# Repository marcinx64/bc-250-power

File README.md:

<div align="center">

# BC-250 power controller

**Turn an AMD BC-250 PC and its ATX supply on and off like a console: front button, web UI, and wake by switching on your game controller.**

</div>

The AMD BC-250 is a mining board built around a cut-down PS5 APU, popular as
a cheap gaming PC. It runs from an ATX supply and has only front-panel pads
for its power and reset buttons. This project is a small controller board (a
Seeed XIAO ESP32-C3 and two dual optocouplers) between the supply and the
BC-250 that makes it behave like a console: one button, a web UI, and
power-on by switching on a game controller.

**Status:** the firmware runs on hand-built perfboard controllers. PCB rev A
is designed (ERC and DRC clean) but not yet fabricated or tested.

## Features

**Power control**
- Front button with LED and buzzer: tap to start or shut down, hold to reset,
  hold longer to cut the power. Hold times, beeps and LED are settings.
- Switches the ATX supply (PS_ON#) and presses the BC-250's power and reset
  buttons; reads its power LED to know the real state.
- Runs from +5VSB, so it is reachable whenever the supply is plugged in.

**Wake on controller**
- Switch on a game controller and the PC starts, with no extra hardware.
- Two methods, chosen on the wake page: **BLE** (any Bluetooth LE controller)
  or **2.4G/BT** (2.4G USB-dongle devices and Bluetooth Classic controllers
  such as the DualShock 4).
- Detection uses the ESP32-C3's own radio through its raw capture engine
  (see Credits). Wake lists hold up to 8 BLE devices, or 8 2.4G dongle
  devices and 2 Bluetooth Classic hosts. The re-arm time stops a controller
  that is left on from restarting the PC after shutdown.

**Web UI**
- Dashboard, power control, event log, settings, network, security, themes.
- Setup wizard on first start (`BC250-Setup` network), password, mDNS name
  `bc250.local`, fixed IP or DHCP, WiFi roaming between access points.
- Debug view with a simulated BC-250, so the whole sequence can be tried on
  the bench.

**Safety and updates**
- Update over WiFi from the browser; the previous firmware stays in the
  other slot. Restart and updates keep the PC running (PS_ON is latched
  through a deliberate restart).
- NTP clock, timezone and quiet hours for the buzzer.
- Automatic OS updates of the BC-250 at night over SSH: a silent start, the
  update, a shutdown. A failed or interrupted update ends with the BC-250
  shut down. The update script handles pacman, rpm-ostree with Flatpak,
  and dnf.
- Password-protected UI and API, recovery gesture for a forgotten password.

**Languages**
- Translatable interface with gettext-style catalogs (`docs/TRANSLATING.md`).
  English and Polish ship first; more are welcome.

## How it works

```mermaid
flowchart LR
  PSU["ATX supply<br/>+5VSB, PS_ON#"] -- "+5VSB (power)" --> C
  C["Controller<br/>XIAO ESP32-C3"] -- "PS_ON# via opto" --> PSU
  C -- "power / reset via opto" --> B["BC-250"]
  B -- "power LED (sense)" --> C
  P["Game controller<br/>BLE / 2.4G / BT Classic"] -. "radio" .-> C
  U["Front button, LED, buzzer"] <--> C
  W["Browser"] -- "WiFi, HTTP" --> C
```

The controller is powered from the supply's standby rail and stays on while
the PC is off. When you press the button, use the UI, or switch on a listed
controller, it turns the supply on, waits for the BC-250's power LED, and
pulses the power button if needed. Shutdown is a power-button pulse; the
controller releases the supply when the LED goes dark. Exact behaviour:
[docs/FINAL_FIRMWARE_SPEC.md](docs/FINAL_FIRMWARE_SPEC.md).

## Supported controllers

<!-- devices:start -->

| Device | Mode | Wake method | Status | Tested on | How to add |
|---|---|---|---|---|---|
| 8BitDo Ultimate 2 Wireless Controller | Bluetooth | Bluetooth LE | Works | 2.1.20 | Wake method Bluetooth: Scan while switching it on, add it. |
| 8BitDo Ultimate 2 Wireless Controller | 2.4G dongle | 2.4G dongle (ESB, 1 Mbit/s) | Works | 2.1.20 | Wake method 2.4G: Learn while switching it on with the dongle unplugged. |
| 8BitDo Ultimate 2C Wireless Controller | 2.4G dongle | 2.4G dongle (ESB, 1 Mbit/s) | Works | 2.1.20 | Wake method 2.4G: Learn while switching it on with the dongle unplugged. |
| Nintendo Switch Pro Controller | Bluetooth (classic) | Bluetooth Classic paging | Expected, untested | - | Wake method 2.4G, Bluetooth hosts: type the BC-250's Bluetooth address (bluetoothctl show on the BC-250), or Learn while switching the controller on. |
| Rii mini i25 keyboard | 2.4G dongle | 2.4G dongle (ESB, 1 Mbit/s) | Works | 2.1.20 | Wake method 2.4G: Learn while switching it on with the dongle unplugged. |
| Sony DualSense | Bluetooth (classic) | Bluetooth Classic paging | Expected, untested | - | Wake method 2.4G, Bluetooth hosts: type the BC-250's Bluetooth address (bluetoothctl show on the BC-250), or Learn while switching the controller on. |
| Sony DualShock 4 | Bluetooth (classic) | Bluetooth Classic paging | Works on a spare board, console test pending | 2.2.16 | Wake method 2.4G, Bluetooth hosts: type the BC-250's Bluetooth address (bluetoothctl show on the BC-250), or Learn while switching the controller on. |
| Valve Steam Controller (2.4G dongle) | 2.4G dongle | Other | Help wanted | - | Record it with the dongle unplugged as in docs/SNIFFING.md and open a new-device issue. |

<!-- devices:end -->

Anything speaking Nordic Enhanced ShockBurst (1 Mbit/s, 5-byte address) should
work in 2.4G mode. Add your device: [devices/README.md](devices/README.md).

## Hardware

The tested build is a 40 x 60 mm perfboard; PCB rev A is in
[hardware/](hardware/README.md). Drawings: [schematic](hardware/schematic.svg),
[wiring](hardware/wiring.svg), [bill of materials](hardware/bom.csv).
Full reference: [docs/HARDWARE.md](docs/HARDWARE.md).

| Part | Qty |
|---|---|
| Seeed XIAO ESP32-C3 | 1 |
| TLP521-2 dual optocoupler (rank GB) | 2 |
| 220 ohm resistor | 3 |
| Active buzzer, 5 V | 1 |
| Illuminated momentary switch (with LED) | 1 |
| Connectors or wires to the ATX plug and the BC-250 headers | |

| XIAO pin | GPIO | Job |
|---|---|---|
| D1 | 3 | PS_ON drive (HIGH = supply on) |
| D2 | 4 | Buzzer + |
| D3 | 5 | BC-250 power LED sense (LOW = lit) |
| D4 | 6 | PWR button (HIGH = pressed) |
| D5 | 7 | RST button (HIGH = pressed) |
| D7 | 20 | Front switch (LOW = pressed) |
| D10 | 10 | Front switch LED (PWM) |

**Two rules that protect the hardware**
- Never connect USB and the ATX +5VSB wire at the same time: the XIAO's 5V pin
  is its USB VBUS.
- A deliberate restart or update keeps the PC running because PS_ON is
  latched. A crash, brown-out or loss of +5VSB still cuts the PC's power.

## Quick start

1. Build the hardware and wire it as in [docs/HARDWARE.md](docs/HARDWARE.md).
   Connect only USB (no ATX) for the first flash.
2. Get the code (`git clone https://github.com/marcinx64/bc-250-power.git`) and flash the firmware over USB:
   [docs/FLASHING.md](docs/FLASHING.md). Later updates go over WiFi from the
   web UI, with a `firmware-<version>.bin` from
   [Releases](https://github.com/marcinx64/bc-250-power/releases) or your own build.
3. Join the `BC250-Setup` network (password `bc250setup`), set a password and
   pick your WiFi in the setup wizard. Then open `http://bc250.local`.
4. On the Wake page choose BLE or 2.4G/BT, press Scan or Learn, switch your
   controller on and add it to the wake list.
5. Unplug USB, connect +5VSB, PS_ON# and the BC-250 wires, and try the button.

## Documentation

| Document | Content |
|---|---|
| [docs/USER_GUIDE.md](docs/USER_GUIDE.md) | Button, LED, web UI, setup, recovery |
| [docs/FLASHING.md](docs/FLASHING.md) | Build, flash over USB, update over WiFi |
| [docs/ESP_IDF_BUILD.md](docs/ESP_IDF_BUILD.md) | ESP-IDF build, settings, memory, boot compatibility |
| [docs/FINAL_FIRMWARE_SPEC.md](docs/FINAL_FIRMWARE_SPEC.md) | Behaviour and HTTP API reference |
| [docs/HARDWARE.md](docs/HARDWARE.md), [hardware/README.md](hardware/README.md) | Perfboard reference, PCB |
| [docs/WAKE_2G4.md](docs/WAKE_2G4.md), [docs/WAKE_BT_CLASSIC.md](docs/WAKE_BT_CLASSIC.md) | How 2.4G and Bluetooth Classic detection works |
| [docs/ADDING_PROTOCOLS.md](docs/ADDING_PROTOCOLS.md) | Add a wake protocol |
| [docs/SNIFFING.md](docs/SNIFFING.md), [devices/README.md](devices/README.md) | Capture a new device, device list |
| [docs/TRANSLATING.md](docs/TRANSLATING.md) | Add a language |
| [docs/TEST_PLAN.md](docs/TEST_PLAN.md), [docs/ROADMAP.md](docs/ROADMAP.md) | Test status, plans |
| [CONTRIBUTING.md](CONTRIBUTING.md), [AGENTS.md](AGENTS.md) | How to contribute, rules for contributors and AI agents |

## Contributing

Translations, new tested devices, wake protocols and hardware improvements
are all welcome; see [CONTRIBUTING.md](CONTRIBUTING.md). The quickest
contributions: translate the UI, or sniff a controller that is not in the
table and open a ["New device" issue](https://github.com/marcinx64/bc-250-power/issues/new/choose).

## Credits

- **[esp-sdr / ESPARGOS](https://github.com/ESPARGOS/esp-sdr)** (GPL-3.0-or-later):
  the undocumented raw capture engine of the ESP32-C3 radio was discovered by
  this project. It is what makes 2.4G and Bluetooth Classic wake possible
  without extra hardware. Thank you.
- Espressif **ESP-IDF** and **NimBLE**.
- **ArduinoJson** by Benoit Blanchon (MIT).
- **[Monocypher](https://monocypher.org)** by Loup Vaillant (BSD-2-Clause or
  CC0-1.0): Ed25519, X25519 and ChaCha20-Poly1305 for the SSH client.

## Author

Marcin K. (GitHub: [marcinx64](https://github.com/marcinx64)).

## License

Copyright Marcin K. (marcinx64). The project is licensed per kind of work,
with texts in [LICENSES/](LICENSES/):

| Part | License |
|---|---|
| Firmware, web UI, tools | [GPL-3.0-or-later](LICENSES/GPL-3.0-or-later.txt) (also required by the esp-sdr capture code) |
| Hardware: KiCad files, schematics, renders, gerbers | [CERN-OHL-S-2.0](LICENSES/CERN-OHL-S-2.0.txt) |
| Documentation, photos, images | [CC-BY-SA-4.0](LICENSES/CC-BY-SA-4.0.txt) |
| Monocypher, kept unmodified in `firmware/bc250_controller/components/monocypher/` | [BSD-2-Clause](LICENSES/BSD-2-Clause.txt) or [CC0-1.0](LICENSES/CC0-1.0.txt), its authors' choice of either |

Each source file names its licence in an SPDX line; [REUSE.toml](REUSE.toml)
covers the rest.

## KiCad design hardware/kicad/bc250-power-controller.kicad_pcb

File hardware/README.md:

# Hardware: PCB rev A

**Status: the rev A PCB has NOT been fabricated or tested yet.** It is a
2-layer layout of the same circuit and GPIO map as the perfboard build. The
perfboard build ([`../docs/HARDWARE.md`](../docs/HARDWARE.md)) is the tested
reference. Expect to find mistakes in rev A; please report them.

Licence: CERN-OHL-S-2.0. Author: Marcin K., github.com/marcinx64.

## What is here

| Path | Content |
|---|---|
| `kicad/bc250-power-controller.kicad_{pro,sch,pcb}` | KiCad 10 project (source of truth) |
| `kicad/bc250.kicad_sym`, `kicad/bc250.pretty`, `kicad/3d` | Project symbols (XIAO, TLP521-2), XIAO footprint and a simple 3D model |
| `kicad/scripts/` | Python generators and `export.sh`, so the design is reproducible |
| `schematic.pdf`, `schematic.svg` | Schematic |
| `renders/` | PCB top, bottom and 3D renders |
| `fab/bc250-power-controller-gerbers.zip` | Gerbers and Excellon drill files (PTH and NPTH) |
| `bom.csv` | Bill of materials with example part numbers |
| `wiring.svg` | Wiring to the ATX plug, the BC-250 and the front switch |
| `hardware.json` | Machine-readable pin map and netlist notes |

## Board

60 x 40 mm, 2 layers, rounded corners, four M3 holes. All parts are
through-hole. The XIAO ESP32-C3 sits on two 1x7 2.54 mm sockets (rows 15.24 mm
apart) with its USB-C connector at the right board edge. A copper keep-out
(no tracks, pour or vias) lies under the XIAO's antenna end; tracks pass above
the module's long side at least 1.3 mm from it. GND is poured on both layers
with stitching vias. Tracks are 0.3 mm for signals and 0.8 mm for +5V and
+5VSB.

Connectors are JST XH (2.5 mm): common, polarised, cheap and easy to crimp.
Screw terminals would need more board area.

| Connector | Pins |
|---|---|
| J1 ATX | 1 PS_ON# (green, ATX pin 16), 2 GND (black, pin 15), 3 +5VSB (purple, pin 9) |
| J2 BC-250 | 1 power LED +, 2 power LED -, 3 power button live pad, 4 reset button live pad |
| J3 front switch | 1 contact NO (white), 2 common (yellow, GND), 3 LED + (red), 4 LED - (black, GND) |

The switch's green NC wire is not used. See [`wiring.svg`](wiring.svg).

## The circuit in short

- **PS_ON# (U1A):** GPIO3 drives an opto LED through R1 (220 R). The opto
  transistor pulls ATX PS_ON# to GND, which turns the supply on.
- **Power and reset buttons (U2):** GPIO6 and GPIO7 drive the LEDs through R2
  and R3. Each opto transistor pulls the button's live pad to GND, like a
  press. Nothing is back-fed into the BC-250.
- **Power LED sense (U1B):** the BC-250 power LED current flows through the
  opto LED, and its transistor pulls GPIO5 (internal pull-up) low while the
  LED is lit.
- **Buzzer:** active buzzer on GPIO4, driven directly (firmware sets maximum
  drive strength).
- **Front switch:** contact on GPIO20 (pull-up, active low), LED on GPIO10 (PWM).
- **Power:** +5VSB from the ATX supply feeds the XIAO 5V pin (= USB VBUS).
  All grounds are common, so the optos switch but do not isolate.
- GPIO2, 8, 9 (strapping) and GPIO21 are unused. The pin map is unchanged
  from the firmware (`firmware/bc250_controller/src/pins.h`).

### Optional parts that fix known issues

| Part | Purpose | As shipped |
|---|---|---|
| R4 (470 R) with jumper JP1 | Limits the LED-sense opto current if the BC-250 LED pads supply more than about 20 mA | JP1 closed, R4 not fitted |
| D1 (1N5819) with jumper JP2 | Schottky diode in the +5VSB line so USB and +5VSB can be connected together | JP2 closed, D1 not fitted |

To use one: fit the part, then cut the thin copper bridge of its jumper on
the top side. The diode costs about 0.3 V, so the XIAO runs from about 4.7 V
instead of 5 V, which is fine for its 3.3 V regulator. **Without D1 fitted
(and JP2 cut), never connect USB and +5VSB at the same time.**

## Bill of materials

| Ref | Qty | Part |
|---|---|---|
| U3 | 1 | Seeed XIAO ESP32-C3, plus 2 x 1x7 female 2.54 mm header (8.5 mm) |
| U1, U2 | 2 | TLP521-2, DIP-8 (LTV-827, PC827, EL827 are pin-compatible); sockets optional |
| R1, R2, R3 | 3 | 220 R 1/4 W axial |
| R4 | 1 | 470 R, optional |
| D1 | 1 | 1N5819, optional |
| BZ1 | 1 | 12 mm active buzzer, 5 V, 7.6 mm pin spacing |
| J1 | 1 | JST B3B-XH-A (+ XHP-3 housing) |
| J2, J3 | 2 | JST B4B-XH-A (+ XHP-4 housings) |
| MH1-4 | 4 | M3 screws and standoffs |

Full list with example part numbers: [`bom.csv`](bom.csv). Part numbers and
distributor SKUs there are suggestions; check them before ordering. The 12 mm
buzzer footprint (12 x 9.5 mm, 7.6 mm pitch) and the XIAO footprint's
dimensions were not checked against physical parts.

## Ordering the PCB

1. Upload `fab/bc250-power-controller-gerbers.zip` to JLCPCB, PCBWay or
   similar. Settings: 2 layers, 60 x 40 mm, 1.6 mm, any solder mask colour,
   HASL or ENIG.
2. Through-hole parts only: no assembly service or stencil is needed.
3. Check the preview: the drill files are `-PTH.drl` and `-NPTH.drl`.
4. The pin-name silkscreen is small (0.55 mm text). Most fabs print it, but a
   larger font may be wanted.

## Assembly and checks

1. Solder low parts first: resistors, then DIP sockets or optos (pin 1 dot
   towards the square pad), the JST headers, the buzzer (+ on the square
   pad), then the XIAO sockets. Fit R4 or D1 only if needed (see above).
2. Do not fit the XIAO yet. With a multimeter in continuity mode check:
   no short between GND and the 3V3 socket pin, and none between GND and the
   5V socket pin.
3. Check continuity from each connector pin to its XIAO socket pin or opto
   pin as in the netlist (`bom` and `schematic.pdf`).
4. Insert the XIAO and U1, U2.
5. **First power-up on USB with nothing else connected** (no ATX, no
   BC-250, no front switch). The board should boot and open its Wi-Fi access
   point as usual; the buzzer beeps.
6. Connect the front switch, then the BC-250 wires, then the ATX supply last
   (without USB).

## Safety rules

- Never connect USB and ATX +5VSB at the same time unless D1 is fitted and
  JP2 is cut.
- The ATX supply must have +5VSB.
- Only the live pad of each BC-250 button is wired; the optos switch it to GND.
- Never start UART0 in firmware: its RX is GPIO20 (front switch).
- Do not use GPIO2, 8, 9 or 21 for anything else.

## Verification status

- ERC: 0 errors, 0 warnings. DRC: 0 violations, 0 unconnected items, schematic
  parity clean. Both with KiCad 10.0.8.
- Not verified: footprint dimensions of the XIAO headers/USB end and the
  buzzer; the 3D XIAO model is a simple stand-in.
- Not tested on real hardware.

## Rebuilding

From the repository root, with KiCad 10 installed as a flatpak: run the
scripts in `kicad/scripts/` (`gen_libs.py`, `gen_sch.py`, then export the
netlist and run `gen_pcb.py`, then `export.sh`). The KiCad files themselves
are the source of truth; edit them in KiCad if you prefer.

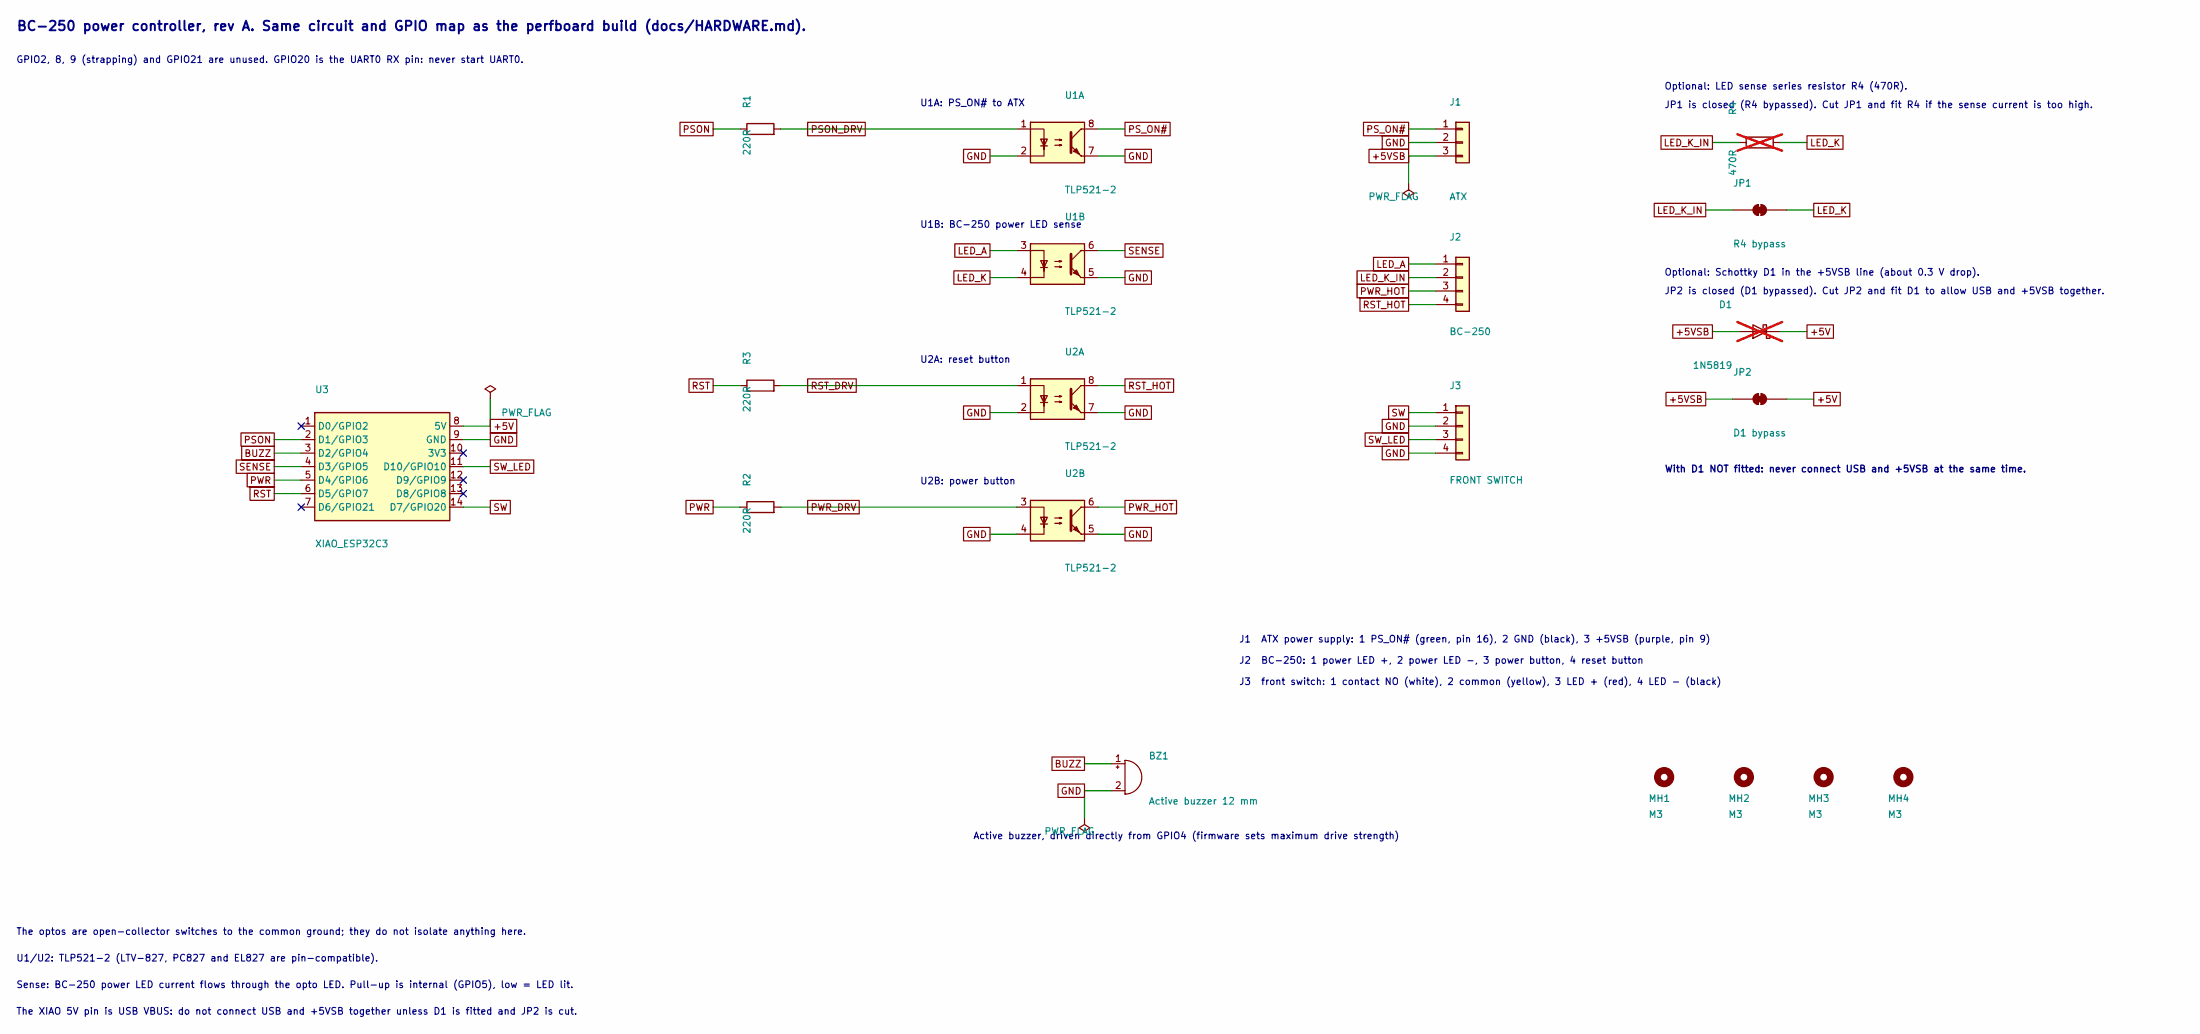
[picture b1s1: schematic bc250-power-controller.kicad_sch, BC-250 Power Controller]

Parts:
BZ1: Active buzzer 12 mm; Buzzer_12x9.5RM7.6
D1: 1N5819; D_DO-41_SOD81_P3.81mm_Vertical_CathodeUp; not fitted
J1: ATX; JST_XH_B3B-XH-A_1x03_P2.50mm_Vertical
J2: BC-250; JST_XH_B4B-XH-A_1x04_P2.50mm_Vertical
J3: FRONT SWITCH; JST_XH_B4B-XH-A_1x04_P2.50mm_Vertical
JP1: R4 bypass; SolderJumper-2_P1.3mm_Bridged_Pad1.0x1.5mm
JP2: D1 bypass; SolderJumper-2_P1.3mm_Bridged_Pad1.0x1.5mm
MH1, MH2, MH3, MH4: M3; MountingHole_3.2mm_M3
R1, R2, R3: 220R; R_Axial_DIN0207_L6.3mm_D2.5mm_P7.62mm_Horizontal
R4: 470R; R_Axial_DIN0204_L3.6mm_D1.6mm_P2.54mm_Vertical; not fitted
U1, U2: TLP521-2; DIP-8_W7.62mm
U3: XIAO_ESP32C3; XIAO_ESP32C3_THT

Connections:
+5V: D1.1 (K), JP2.2 (B), U3.8 (5V)
+5VSB: D1.2 (A), J1.3, JP2.1 (A)
BUZZ: BZ1.1 (+), U3.3 (D2/GPIO4)
GND: BZ1.2 (-), J1.2, J3.2, J3.4, U1.2, U1.5, U1.7, U2.2, U2.4, U2.5, U2.7, U3.9 (GND)
LED_A: J2.1, U1.3
LED_K: JP1.2 (B), R4.2, U1.4
LED_K_IN: J2.2, JP1.1 (A), R4.1
PSON: R1.1, U3.2 (D1/GPIO3)
PSON_DRV: R1.2, U1.1
PS_ON#: J1.1, U1.8
PWR: R2.1, U3.5 (D4/GPIO6)
PWR_DRV: R2.2, U2.3
PWR_HOT: J2.3, U2.6
RST: R3.1, U3.6 (D5/GPIO7)
RST_DRV: R3.2, U2.1
RST_HOT: J2.4, U2.8
SENSE: U1.6, U3.4 (D3/GPIO5)
SW: J3.1, U3.14 (D7/GPIO20)
SW_LED: J3.3, U3.11 (D10/GPIO10)

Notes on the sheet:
U1A: PS_ON# to ATX
U1B: BC-250 power LED sense
U2A: reset button
U2B: power button
J1 ATX power supply: 1 PS_ON# (green, pin 16), 2 GND (black), 3 +5VSB (purple, pin 9)
J2 BC-250: 1 power LED +, 2 power LED -, 3 power button, 4 reset button
J3 front switch: 1 contact NO (white), 2 common (yellow), 3 LED + (red), 4 LED - (black)
Optional: LED sense series resistor R4 (470R).
JP1 is closed (R4 bypassed). Cut JP1 and fit R4 if the sense current is too high.
Optional: Schottky D1 in the +5VSB line (about 0.3 V drop).
JP2 is closed (D1 bypassed). Cut JP2 and fit D1 to allow USB and +5VSB together.
With D1 NOT fitted: never connect USB and +5VSB at the same time.
Active buzzer, driven directly from GPIO4 (firmware sets maximum drive strength)
BC-250 power controller, rev A. Same circuit and GPIO map as the perfboard build (docs/HARDWARE.md).
GPIO2, 8, 9 (strapping) and GPIO21 are unused. GPIO20 is the UART0 RX pin: never start UART0.
The optos are open-collector switches to the common ground; they do not isolate anything here.
U1/U2: TLP521-2 (LTV-827, PC827 and EL827 are pin-compatible).
Sense: BC-250 power LED current flows through the opto LED. Pull-up is internal (GPIO5), low = LED lit.
The XIAO 5V pin is USB VBUS: do not connect USB and +5VSB together unless D1 is fitted and JP2 is cut.

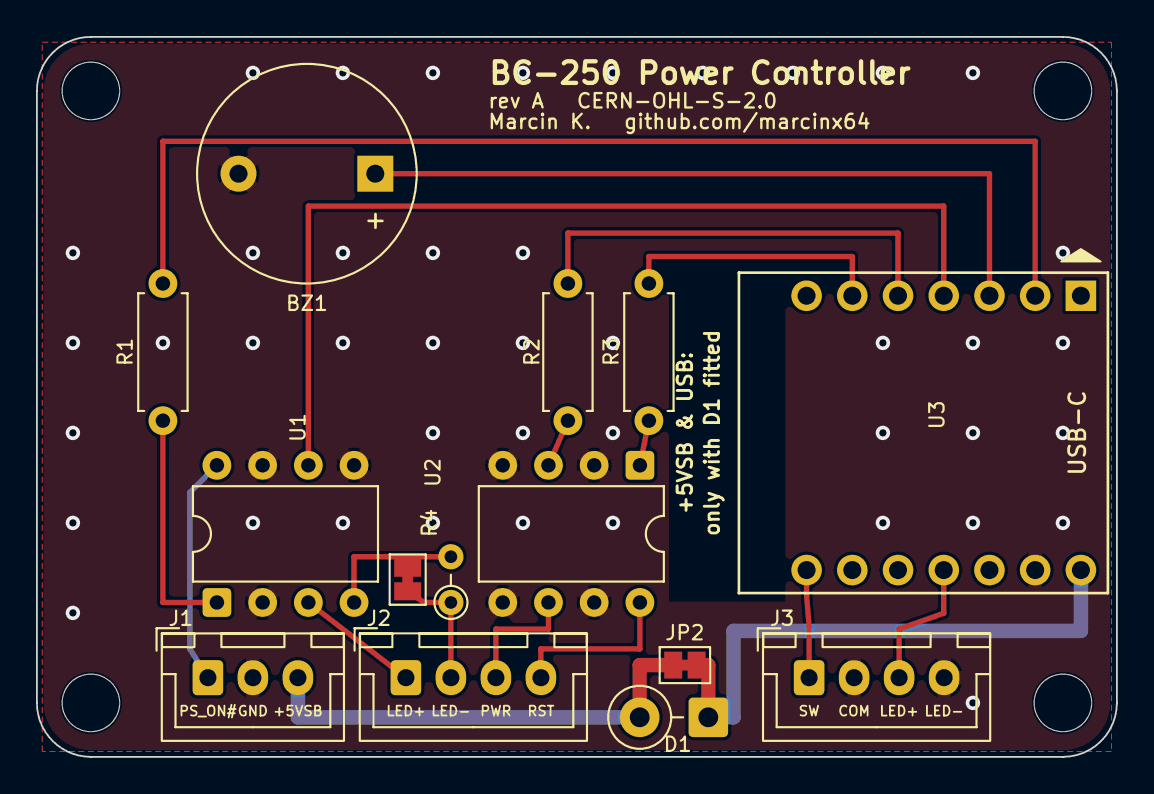
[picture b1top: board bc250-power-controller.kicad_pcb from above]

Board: 2 copper layers, 60.0 x 40.0 mm, 18 parts (0 on the bottom side), 19 nets.

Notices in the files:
README.md:
Firmware: GPL-3.0-or-later
Hardware: CERN-OHL-S-2.0
Docs: CC BY-SA 4.0
hardware/kicad/bc250-power-controller.kicad_pcb:
rev A CERN-OHL-S-2.0
hardware/kicad/bc250-power-controller.kicad_sch:
License: CERN-OHL-S-2.0
